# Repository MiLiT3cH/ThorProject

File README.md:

# The Thor Project

Benvenuti nel mio progetto di retrofitting dei fari Thor Hammer 2020 sulla mia Volvo V40 2013 nata con i fari alogeni di serie.  
In rete si trovano parecchie dicerie su come ciò sia impossibile.  
Ho deciso di mettermi in gioco e scoprire se davvero è così. 😉

## Changelog:

### 21/05/2025
- Resoconto: Dopo la realizzazione del progetto, ha resistito perfettamente per ben 3 Mesi;
             Di recente si sono guastate le luci anabaglianti.
- Problema: Durante il teardown di uno dei due fari (si sono guastati entrambi);
            Ho notato il diodo Led bruciato.
- Causa: Errore umano... All'interno del faro era presente una ventola di raffreddamento che non è stata cablata;
         In sintesi: I Led si sono guastati per surriscaldamento
- Realizzazione PCB V4 
- Aggiornamento Pinout connettore faro
- Aggiunto Datasheet led 

### 19/12/2024
- Risolta la problematica: protezione posizioni durante la freccia
- Aggiornamento Resoconto
- Costruzione cablaggio per connettore originale
- Test Funzionale: superato
- Aggiornamento Resoconto Schede V2

### 27/10/2024
- Ultimi preparativi Schede V2
- Resoconto Schede V2
- Corretti i voltaggi dei Led

## 13/10/2024
- centraline V2 completate
- test montaggio completato 
- problematica con la resistenza del baffo di posizione (rivedere schede)

### 28/09/2024:
- Una centralina è già stata realizzata
- Fase di test
- Inizio progettazione centralina lato sinistro

### 18/08/2024:
- Ho mollato il progetto per parecchio tempo e l'ho riesumato pochi giorni fa
  potrebbero esserci nuove notizie a breve.
- Prototipazione nuova scatola da stampare in 3D per ospitare la nuova board

### 21/11/2023:
- Modifica assorbimento massimo centraline
- Assemblaggio centraline
- Primo test completo su macchina

### 13/11/2023:
- Cambio radicale approccio 
- Costruzione e test centralina artigianale
- Pinout aggiornato

### 13/10/2023:
- Aggiunto Schema controller a relè (da provare)
- Aggiunta Schema ladder per testare la logica del controller relè
- Aggiunti Datasheet (mosfet, rectifier)
- Aggiornato Schema

### 11/10/2023:
- Effettuate misurazioni interne al faro per capire i pin di collegamento del motore livellamento fari
- Aggiornamento Pinout
- Aggiunto Datasheet MCU
- Aggiunto Pinout Connettore Macchina
- Aggiunto Pinout Connettore Faro (Thor) (versione 1)

### 09/10/2023:
- Assemblaggio seconda centralina modificata e test
- Aggiunta Foto risultato
- Bug: l'anabbagliante si accende quando in automatico senza input
- Misurata tensione uscita lampada: 46v

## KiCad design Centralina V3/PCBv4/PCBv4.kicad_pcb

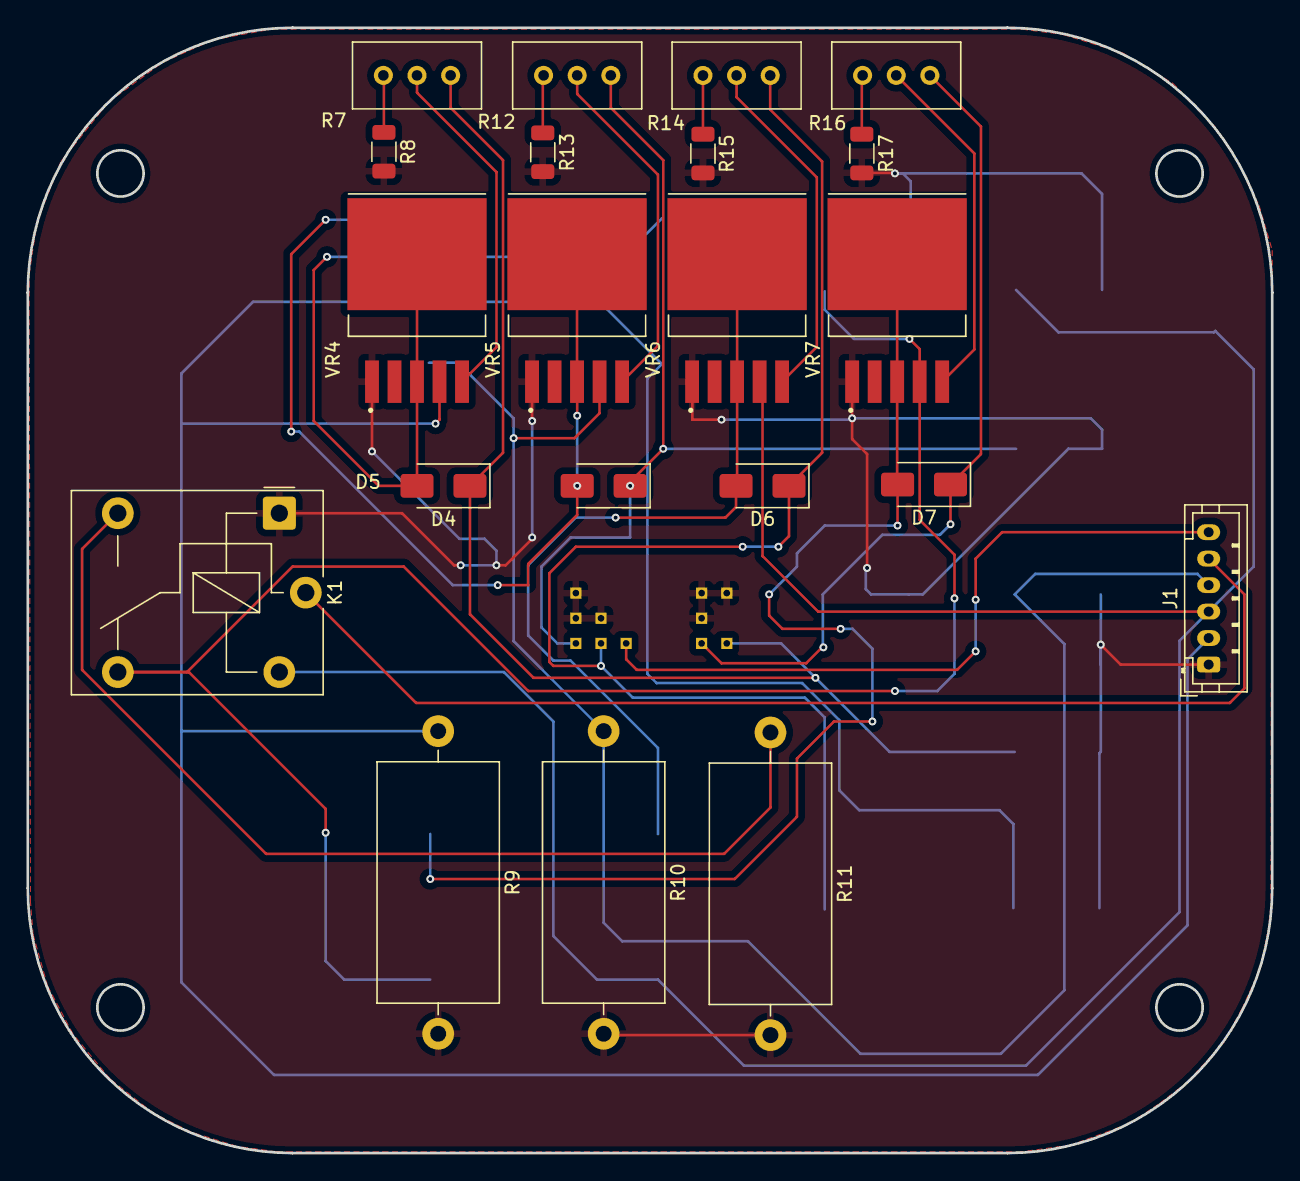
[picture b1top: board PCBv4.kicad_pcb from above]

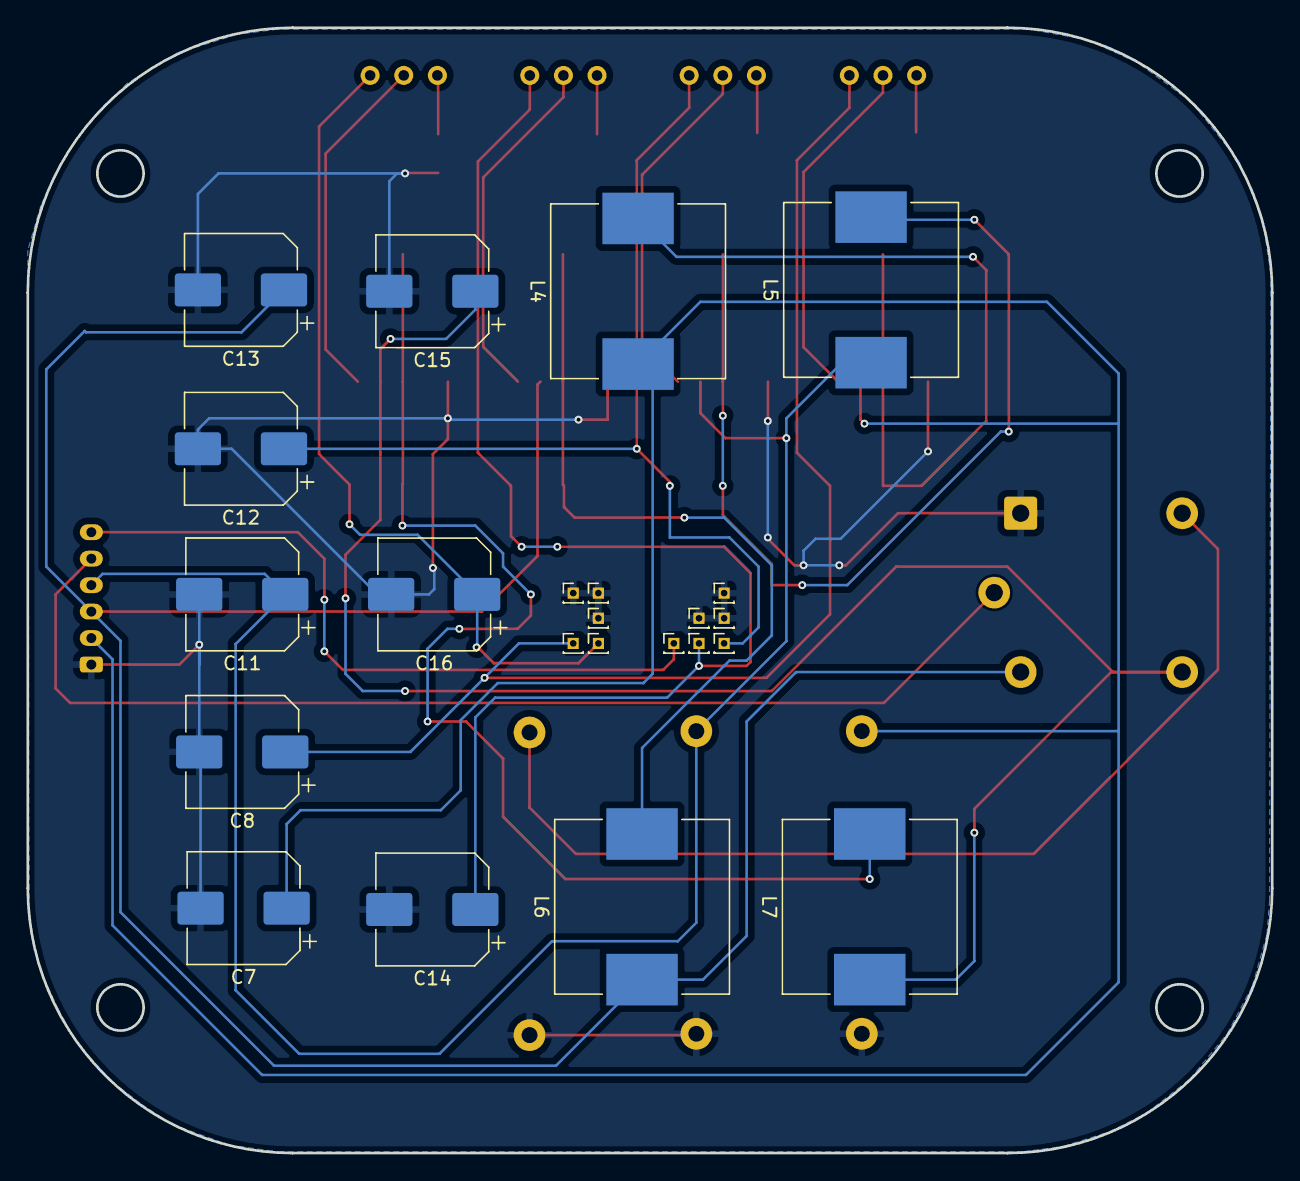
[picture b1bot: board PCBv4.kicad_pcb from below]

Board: 2 copper layers, 94.0 x 85.0 mm, 44 parts (23 on the bottom side), 24 nets.

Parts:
C7, C11, C13, C15: 220uF_50V; CP_Elec_8x10
C8, C12, C14, C16: 100uF_50V; CP_Elec_8x10
D4, D5, D6, D7: SS14; D_SMA
J1: Conn_01x06_Pin; JST_PH_B6B-PH-K_1x06_P2.00mm_Vertical
J2, J3, J4, J5, J6, J7, J8, J9, J10, J11, J12: PinHeader_1x01_P1.00mm_Vertical_edit
K1: Relay_SPDT; Relay_SPDT_Finder_36.11
L4, L5, L6, L7: 33UH; L_Neosid_SM-NE127_HandSoldering
R7, R12, R14, R16: 10K; Potentiometer_Bourns_3296W_Vertical
R8, R13, R15, R17: 330ohm; R_1206_3216Metric
R9, R10: 120Ω; R_Axial_DIN0918_L18.0mm_D9.0mm_P22.86mm_Horizontal
R11: 39Ω; R_Axial_DIN0918_L18.0mm_D9.0mm_P22.86mm_Horizontal
VR4, VR5, VR6, VR7: XL6009; DPAK170P1435X465-6N

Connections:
GND: C7.2, C8.2, C11.2, C12.2, C13.2, C14.2, C15.2, C16.2, J1.1, J7.1, J8.1, J9.1, J10.1, J11.1, J12.1, K1.A1, R8.2, R9.2, R10.2, R11.2, R13.2, R15.2, R17.2, VR4.1 (GND), VR5.1 (GND), VR6.1 (GND), VR7.1 (GND)
unnamed: D4.2 (A), L4.2, VR4.3 (SW), VR4.6 (SW)
unnamed: D5.2 (A), L5.2, VR5.3 (SW), VR5.6 (SW)
unnamed: D6.2 (A), L6.2, VR6.3 (SW), VR6.6 (SW)
unnamed: D7.2 (A), L7.2, VR7.3 (SW), VR7.6 (SW)
unnamed: J1.5, K1.11
unnamed: K1.14, R11.1
unnamed: R7.2 (b), VR4.5 (FB)
unnamed: R7.3 (c), R8.1
unnamed: R12.2 (b), VR5.5 (FB)
unnamed: R12.3 (c), R13.1
unnamed: R14.2 (b), VR6.5 (FB)
unnamed: R14.3 (c), R15.1
unnamed: R16.2 (b), VR7.5 (FB)
unnamed: R16.3 (c), R17.1
VCC_Anabaglianti: C7.1, J1.2, L4.1, R9.1, VR4.4 (VIN)
VCC_Freccia: C13.1, J1.3, K1.A2, L6.1, VR6.4 (VIN)
VCC_Posizione: C15.1, K1.12, L7.1, VR7.4 (VIN)
Vcc_Abaglianti: C11.1, J1.4, L5.1, R10.1, VR5.4 (VIN)
Vcc_Alzafari: J1.6, J4.1
Vout_1: C12.1, D5.1 (K), J2.1, R12.1 (a)
Vout_2: C14.1, D6.1 (K), J3.1, R14.1 (a)
Vout_3: C8.1, D4.1 (K), J6.1, R7.1 (a)
Vout_4: C16.1, D7.1 (K), J5.1, R16.1 (a)

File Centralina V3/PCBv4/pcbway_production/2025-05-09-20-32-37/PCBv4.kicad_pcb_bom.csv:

Designator,Quantity,Value,Footprint,Package,MPN,DNP,Mount_Type,Description,Sim.Pins,Sim.Device,Sim.Params,Indicator,MP
"C11, C13, C15, C7",4,220uF_50V,CP_Elec_8x10,,,,smt,"220uF, 50V Electrolytic Capacitor",,,,,
"C12, C14, C16, C8",4,100uF_50V,CP_Elec_8x10,,,,smt,"100uF, 50V Electrolytic Capacitor",,,,,
"D4, D5, D6, D7",4,SS14,D_SMA,,,,smt,"40V 1A Schottky Diode, SMA",,,,,
J1,1,Conn_01x06_Pin,JST_PH_B6B-PH-K_1x06_P2.00mm_Vertical,,,,tht,"Generic connector, single row, 01x06, script generated",,,,,
"J10, J11, J12, J2, J3, J4, J5, J6, J7, J8, J9",11,~,PinHeader_1x01_P1.00mm_Vertical_edit,,,,tht,"Generic connector, single row, 01x01, script generated (kicad-library-utils/schlib/autogen/connector/)",,,,,
K1,1,Relay_SPDT,Relay_SPDT_Finder_36.11,,,,tht,"Relay SPDT, monostable, EN50005",,,,,
"L4, L5, L6, L7",4,33UH,L_Neosid_SM-NE127_HandSoldering,,,,smt,Inductor with ferrite core,,,,,
"R10, R9",2,120Ω,R_Axial_DIN0918_L18.0mm_D9.0mm_P22.86mm_Horizontal,,,,tht,5W Resistor,,,,,
R11,1,39Ω,R_Axial_DIN0918_L18.0mm_D9.0mm_P22.86mm_Horizontal,,,,tht,5W Resistor,,,,,
"R12, R14, R16, R7",4,10K,Potentiometer_Bourns_3296W_Vertical,,,,tht,potentiometer with movable/rotating/sliding contact (IEEE zigzag),1=1 2=2 3=3,SPICE,"type=""A"" model=""lin100k"" lib=""R-potentiometer.lib""",●,
"R13, R15, R17, R8",4,330ohm,R_1206_3216Metric,,,,smt,"330Ω, 1/4W Resistor",,,,,
"VR4, VR5, VR6, VR7",4,XL6009,DPAK170P1435X465-6N,,,,smt,DCDCstepup,,,,,XL6009

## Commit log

2023-10-07 Work in progress
2023-10-07 File di Analisi
2023-10-07 Pinout Verificato parte DX
2023-10-10 Aggiornamento Pinout
2023-10-10 Nuovi Pinout Aggiunti
2023-10-10 Aggiunto Datasheet MCU
2023-10-10 Test Centralina
2023-10-10 Pinout connettore auto
2023-10-11 Modifica comando singolo driver
2023-10-11 test interblocco alimentazioni
2023-10-11 info aggiornate
2023-10-13 schema controller a relè aggiunto
2023-10-13 changelog aggiornato
2023-10-13 schema ladder logica controller relè
2023-10-13 Schema aggiornato
2023-10-13 datasheet aggiornati
2023-11-13 Pinout Aggiornato
2023-11-13 aggiornamento generale
2023-12-28 Cerco Di Rendere il tutto più carino
2024-08-17 Thor project v2?
2024-09-28 Aggiornamenti
2024-10-13 aggiornamento
2024-10-27 Aggiornameto
    dettagli Schede V2
2024-12-20 Aggiornamento 20/12/24
2025-05-21 Update 21/05/2025
    Inizio Centraline V4
2025-05-21 Update 21/05/2025
    Inizio Centralina V4
2025-05-21 Update 21/05/2025
